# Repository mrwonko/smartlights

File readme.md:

# Smart Home Intent Transmission

My S.H.I.T. Smartlights.

There's a chance you found this by coming across my hardware in real life. That'd be pretty cool.

This is an attachment for the Raspberry Pi Zero for Google Home-controlled lights. It's not technically a Pi HAT because it doesn't include the software for the Pi (that needs to be installed separately) and you're not supposed to power the Pi itself, as power is provided through this attachment. It also supports the installation of switches and comes with a power button for the Pi.

## Known Bugs

### Revision 2.4

* RGB LED strips are incorrectly assumed to share GND instead of 12V
* the transistors Q1-Q6 are wired incorrectly
* J1-J4 assume a slightly too small footprint

This can be manually patched by changing the center pin of the transistors from 12V to GND, and changing the GND on J1-J4 to 12V. To retain correct pin order on J1-J4, they also need to be installed with 180° rotation. This in turn means they slightly overlap with the transistors, unless those are installed at a slight angle.

## Next steps

* implement state pushing
* implement state querying
* write my own unsafe but fast GPIO library
* use that library in clients to implement single-threaded flicker-free PWM dimming
* implement RGB lights
  * white calibration
* implement buttons
* implement animations ("scenes")

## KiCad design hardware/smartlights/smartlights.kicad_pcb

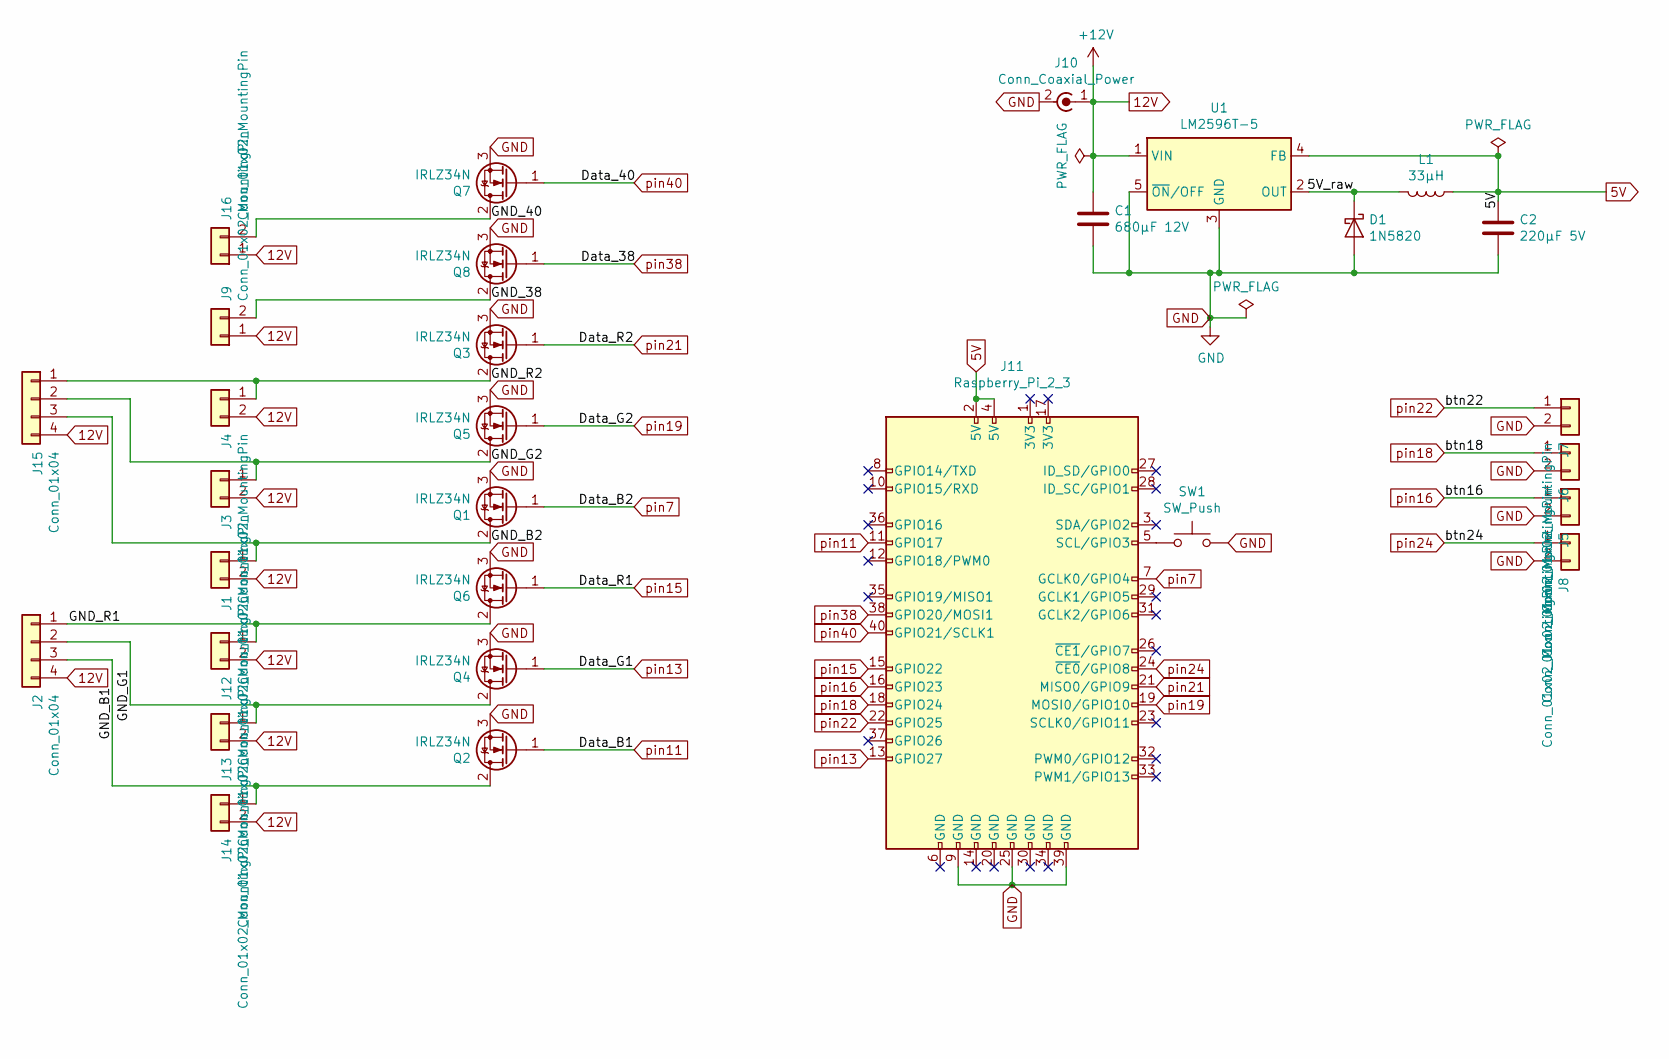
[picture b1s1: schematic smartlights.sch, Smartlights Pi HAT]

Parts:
C1: 680µF 12V; CP_Radial_D10.0mm_P5.00mm
C2: 220µF 5V; CP_Radial_D6.3mm_P2.50mm
D1: 1N5820; D_DO-201AD_P15.24mm_Horizontal
J1, J3, J4, J5, J6, J7, J8, J9, J12, J13, J14, J16: Conn_01x02_MountingPin; PinHeader_1x02_P2.54mm_Vertical_Lock
J2, J15: Conn_01x04; PinHeader_1x04_P2.54mm_Vertical_Lock
J10: Conn_Coaxial_Power; BarrelJack_Horizontal
J11: Raspberry_Pi_2_3; Raspberry_Pi_Zero_Socketed_THT_FaceDown_MountingHoles
L1: 33µH; L_Radial_D12.5mm_P7.00mm_Fastron_09HCP
Q1, Q2, Q3, Q4, Q5, Q6, Q7, Q8: IRLZ34N; TO-252AA
SW1: SW_Push; SW_PUSH_6mm
U1: LM2596T-5; TO-263-5_TabPin3

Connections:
5V: C2.1, J11.2 (5V), J11.4 (5V), L1.1, U1.4 (FB)
12V: C1.1, J1.2, J2.4, J3.2, J4.2, J9.1, J10.1 (In), J12.2, J13.2, J14.2, J15.4, J16.1, U1.1 (VIN)
/5V_raw: D1.1 (K), L1.2, U1.2 (OUT)
/GND_38: J9.2, Q8.2 (D)
/GND_40: J16.2, Q7.2 (D)
/GND_B1: J2.3, J14.1, Q2.2 (D)
/GND_B2: J1.1, J15.3, Q1.2 (D)
/GND_G1: J2.2, J13.1, Q4.2 (D)
/GND_G2: J3.1, J15.2, Q5.2 (D)
/GND_R1: J2.1, J12.1, Q6.2 (D)
/GND_R2: J4.1, J15.1, Q3.2 (D)
GND: C1.2, C2.2, D1.2 (A), J5.2, J6.2, J7.2, J8.2, J10.2 (Ext), J11.9 (GND), J11.25 (GND), J11.39 (GND), Q1.3 (S), Q2.3 (S), Q3.3 (S), Q4.3 (S), Q5.3 (S), Q6.3 (S), Q7.3 (S), Q8.3 (S), SW1.2, U1.3 (GND), U1.5 (~ON~/OFF)
unnamed: J11.5 (SCL/GPIO3), SW1.1
pin7: J11.7 (GCLK0/GPIO4), Q1.1 (G)
pin11: J11.11 (GPIO17), Q2.1 (G)
pin13: J11.13 (GPIO27), Q4.1 (G)
pin15: J11.15 (GPIO22), Q6.1 (G)
pin16: J5.1, J11.16 (GPIO23)
pin18: J6.1, J11.18 (GPIO24)
pin19: J11.19 (MOSI0/GPIO10), Q5.1 (G)
pin21: J11.21 (MISO0/GPIO9), Q3.1 (G)
pin22: J7.1, J11.22 (GPIO25)
pin24: J8.1, J11.24 (~CE0~/GPIO8)
pin38: J11.38 (GPIO20/MOSI1), Q8.1 (G)
pin40: J11.40 (GPIO21/SCLK1), Q7.1 (G)

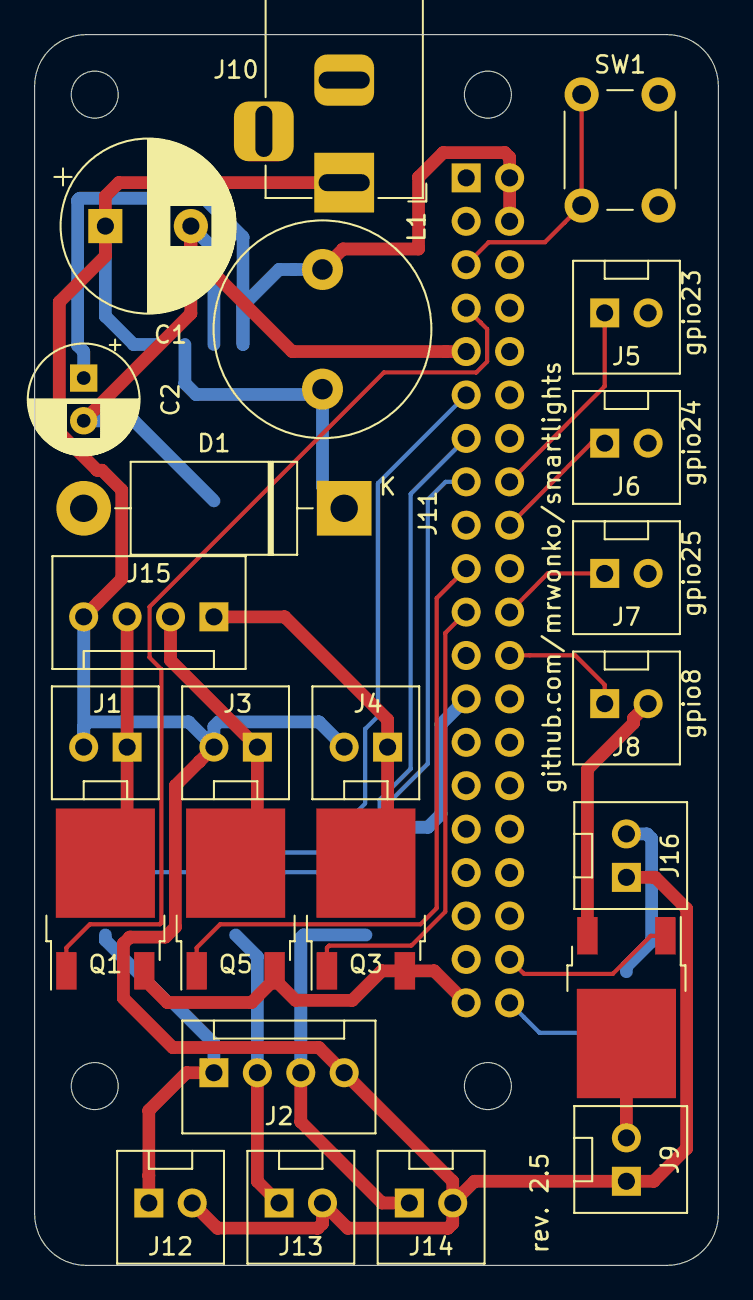
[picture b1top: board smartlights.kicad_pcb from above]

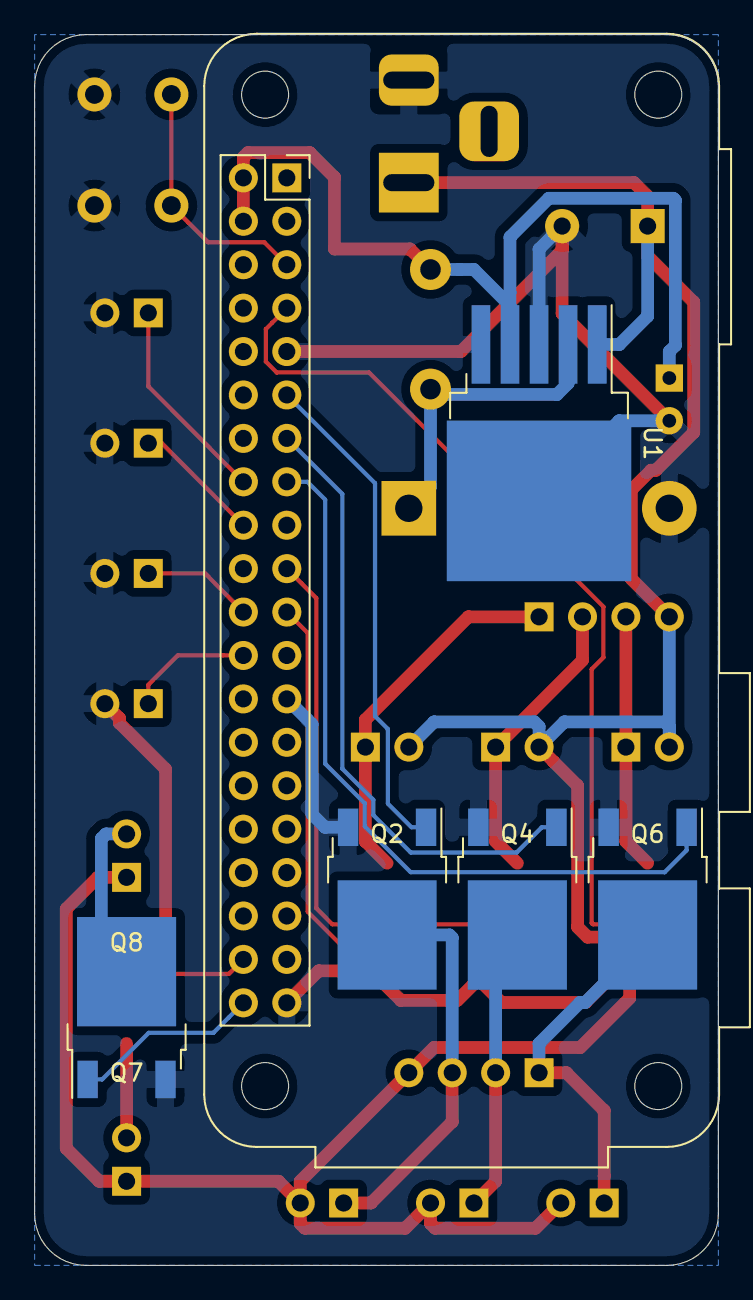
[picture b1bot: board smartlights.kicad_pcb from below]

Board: 2 copper layers, 40.0 x 72.0 mm, 30 parts (6 on the bottom side), 25 nets.

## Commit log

2019-02-10 Add RasPi light "hello software PWM world"
2019-02-10 Add simple oauth2 server
    Since apparently that's necessary for Google actions.
2019-02-10 Add user name to access_token
2019-02-10 Use Authorization Code OAuth grant flow
    This is what Google Assitant Actions use, apparently.
    Using a custom variant of JWTs as tokens.
2019-02-17 Implement SYNC response
2019-02-17 Request SYNC on startup
2019-02-18 Implement executing OnOff commands
2019-02-18 Ack received messages and discard old ones
    Fixes lights mysteriously turning on and off after a while.
2019-02-24 Add new Shoe & LP lights
2019-04-25 WIP: implementing the Query command
    So Google Home can check a light's state.
2019-04-25 add placeholder benchmark
2019-04-25 Benchmark pin toggling with and without mutex
2019-11-21 Log request body on Sync request error
    I currently receive 400 errors from Google when trying to turn on my lights.
2019-11-21 Add go version to module file
    The latest Go version adds it automatically.
2019-11-21 Update & tidy modules
2019-11-28 graceful lightserver shutdown
2019-11-28 log receive errors
2019-11-28 remove dead code
2019-12-05 State report proof-of-concept
    This can successfully authenticate towards the Google API, but doesn't cache the
    access token and sends no payload.
2020-03-05 Add PCB design for hardware platform
    This is a Raspberry Pi Zero W HAT.
    Create usind KiCAD.
2020-03-12 Add switches to PCB, enlarging it.
2020-03-12 Neaten up labels, GND area
2020-03-12 Re-propagate
2020-03-26 PCB: Use RasPi footprint, reduce GND area around jacks
2020-03-28 Add power button and connect more 5V/GND pins. For beaut.
2020-03-28 Add not-a-HAT note
2020-03-31 Move back print to front to reduce manufacturing costs
2020-04-04 Fix wrong voltage on transistors
    Also, the RGB Strip has shared 12V, not GND.
2020-04-04 Forgot to add the latest schema
2020-04-16 Update lights to new hardware platform
    Also removed the lights that have been disconnected since I physically moved
    them.
2020-04-26 SMD Rework
    - removed one button to make space
    - slightly larger PCB dimensions
    - SMD transistor & voltage regulator
    - access to individual RGB channels
    - second RGB output
    - two additional single-color outputs
2020-04-26 Add Readme
2020-04-27 Add Kitchen Pi with Sink Light
2020-04-27 Add Pi config to piclient
    So there can be multiple distinct instances
2020-04-28 Clean up fulfillment handler
    Split into separate functions, improved execute error handling & response
    terseness. Added TODOs.
2020-04-29 Add TODO about improving PubSub messaging
2020-04-30 Rename internal/common to pubsubhelper
2020-04-30 Move JSON types to internal/protocol
2020-05-07 Add RGB Liquor Lights
    With workaround of using individual lights, until I implement dimming & RGB
    lights properly.
2020-05-16 Add Shelf RGB Light
2020-07-02 Shut down on fatal receive error
    Every now an then this happens:
    > oauth2: cannot fetch token: Post "https://oauth2.googleapis.com/token": dial tcp: i/o timeout
    That's usually transient, but instead of building some complex retry logic,
    let's just die and let systemd restart us.
2020-07-30 Change Execute protocol to allow multiple commands per message
    It's now very close to the format of incoming requests, just partitioned by
    target Pi.
2020-07-30 Add next steps
    Because I often put this project on ice for months and forget what I was doing.
2020-10-15 Fix broken protocol test after type change
2020-10-15 Cache access tokens for state reporting
2020-12-15 Add Logo
    I created these files a long time ago, I think they might have been necessary to
    create the GCP project?
2020-12-15 Add forgotten benchmark file
    should've been included in original commit
2020-12-15 Add personal deploy scripts
    These are not meant to be usable by anyone but me.
2020-12-17 Remove resolved TODO about batching execute messages
    This has been implemented.
2020-12-17 Improve Server main error handling
2021-03-07 Fix fulfilment error handling panic
    Appended the wrong error, which was always nil.
2021-06-19 Add Dance Mat Proof of Concept
    Trying out a library to poll my dance mat controller. Works.
2021-06-19 Rudimentary dance mat light controls
    Inefficient due to polling, so I should roll this back after Maraoke
2022-09-27 replace deprecated JWT library
2022-09-27 quick & dirty report & query implementation
    fixes being unable to toggle lights in the Google Home app
2023-02-25 Bump golang.org/x/crypto from 0.0.0-20190605123033-f99c8df09eb5 to 0.1.0
    Bumps [golang.org/x/crypto](https://github.com/golang/crypto) from 0.0.0-20190605123033-f99c8df09eb5 to 0.1.0.
    - [Release notes](https://github.com/golang/crypto/releases)
    - [Commits](https://github.com/golang/crypto/commits/v0.1.0)
    ---
    updated-dependencies:
    - dependency-name: golang.org/x/crypto
2023-12-18 Bump golang.org/x/crypto from 0.1.0 to 0.17.0
    Bumps [golang.org/x/crypto](https://github.com/golang/crypto) from 0.1.0 to 0.17.0.
    - [Commits](https://github.com/golang/crypto/compare/v0.1.0...v0.17.0)
    ---
    updated-dependencies:
    - dependency-name: golang.org/x/crypto
    dependency-type: direct:production
2024-11-02 configure .sh line endings
2024-11-02 do not link glibc
2024-11-02 request report of uncached devices on query
    This should fix the issue where if the piclient is offline when the
    lightserver starts, its state is never requested and thus never
    reported, so it is unusable.
2024-11-02 report state on piclient start
    This should also address the issue of the server not knowing a client's
    state if it starts first.
